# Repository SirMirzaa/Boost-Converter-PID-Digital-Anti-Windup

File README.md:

# Boost Converter dengan Kontrol PID Digital + Anti-Windup
Teknologi Rekayasa Instrumentasi dan Kontrol, SV UGM.

Proyek ini punya dua tahap dengan spesifikasi berbeda:

1. **Simulasi (UTS): paket PBL-B dari dosen**, 24 V → 48 V. Sudah selesai di Simulink (`simulink/`).
2. **Hardware (UAS): reverse engineering modul MT3608**, 12 V → 24 V. Board dibuat dengan MOSFET dan gate driver diskret, dikendalikan RP2040 dengan PID digital + anti-windup. Telemetri dikirim ke board IoT (ESP32-C3) lewat UART.

## Spesifikasi hardware (reverse MT3608)

| Parameter | Nilai |
|---|---|
| Vin | 12 V (adaptor 12 V 2 A) |
| Vout (Vref) | 24 V (bisa diatur, maks 28 V) |
| fsw | 300 kHz |
| Induktor | 22 µH, CD54 (dicopot dari modul MT3608) |
| Beban | 220 Ω dan 110 Ω (2 × 220 Ω paralel) |
| Iout nominal | ±0,22 A (110 Ω) |
| Gangguan | 220 Ω → 110 Ω |
| Ripple Vout | ≤ 0,48 Vpp (2 %) |

Arus dibatasi induktor CD54 (arus saturasi sekitar 1–1,5 A). Converter bekerja di batas CCM/DCM, sama seperti MT3608 di beban ringan.

## Spesifikasi simulasi (PBL-B, sudah selesai)

| Parameter | Nilai |
|---|---|
| Vin | 24 V (uji 20 / 24 / 28 V) |
| Vref | 48 V |
| fsw | 20 kHz |
| Beban | 32 Ω nominal, uji 16–64 Ω |
| Ripple Vout | ≤ 0,96 Vpp |
| Gangguan | 32 Ω → 16 Ω pada t = 0,05 s |

## Progres

- [x] Perhitungan dan model Simulink PBL-B (open-loop, closed-loop)
- [x] Tuning PID, 8 kombinasi gain (`simulink/tuning_pid.m`)
- [x] Skrip uji skenario (`simulink/uji_skenario.m`)
- [x] Revisi skematik KiCad ke spek MT3608 (ERC bersih)
- [x] Footprint CD54 + model 3D
- [ ] Simulink untuk spek hardware (12 V → 24 V, 300 kHz, 22 µH)
- [ ] Verifikasi Proteus (gate driver)
- [ ] Layout dan routing PCB, cetak PCB
- [ ] Firmware RP2040 (PWM 300 kHz, PID, telemetri UART)
- [ ] Uji hardware dan perbandingan dengan modul MT3608 asli

## Struktur repo

```
docs/        rencana kerja, perhitungan, laporan, gambar
simulink/    model .slx + skrip .m (PBL-B)
hardware/    kicad/ (skematik, PCB, footprint, model 3D), proteus/, BOM.csv
firmware/    kode RP2040 (PID digital + anti-windup, telemetri ke ESP32-C3)
data/        hasil pengukuran / log telemetri (.csv)
```

Rencana kerja: [docs/PLANNING.md](docs/PLANNING.md) · Daftar komponen: [hardware/BOM.csv](hardware/BOM.csv) · Panduan Simulink: [docs/SIMULINK_GUIDE.md](docs/SIMULINK_GUIDE.md)

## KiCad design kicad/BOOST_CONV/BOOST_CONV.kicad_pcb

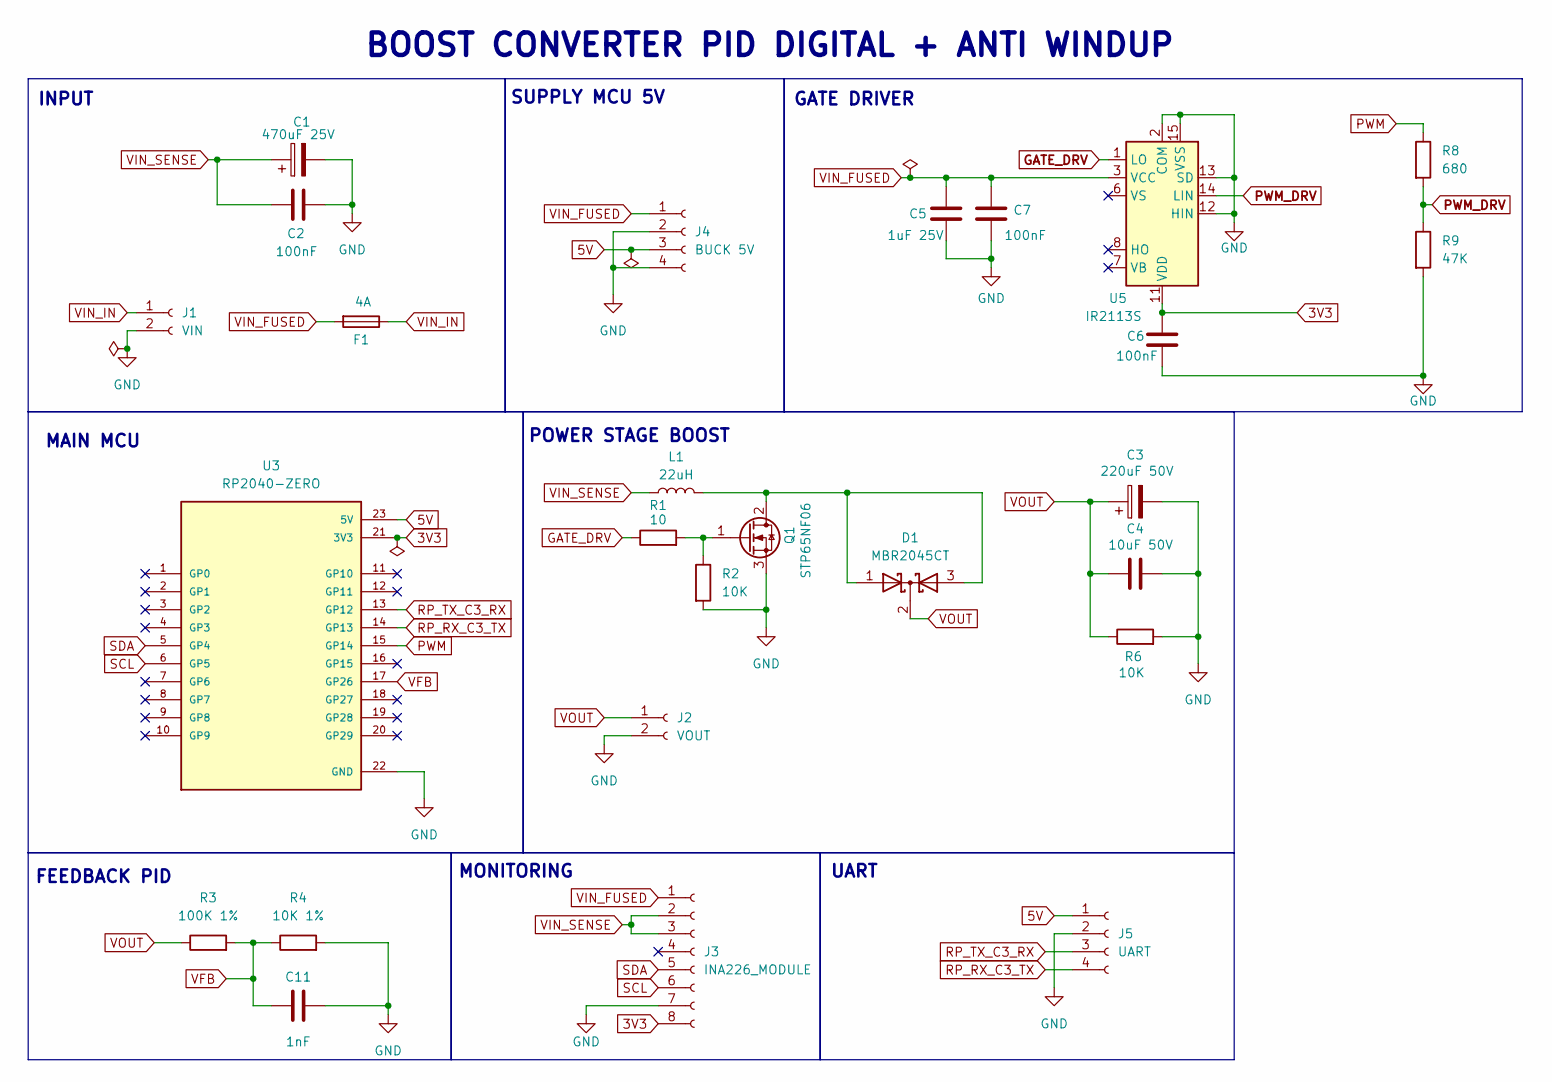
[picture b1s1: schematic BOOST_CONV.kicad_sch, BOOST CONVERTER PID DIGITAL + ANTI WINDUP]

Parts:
C1: 470uF 25V; CP_Radial_D10.0mm_P5.00mm
C2, C6, C7: 100nF; C_1206_3216Metric
C3: 220uF 50V; CP_Radial_D12.5mm_P5.00mm
C4: 10uF 50V; C_1206_3216Metric
C5: 1uF 25V; C_1206_3216Metric
C11: 1nF; C_1206_3216Metric
D1: MBR2045CT; TO-220-3_Vertical
F1: 4A; Fuseholder_Cylinder-5x20mm_Bulgin_FX0457_Horizontal_Closed
J1: VIN; TerminalBlock_Phoenix_MKDS-1,5-2_1x02_P5.00mm_Horizontal
J2: VOUT; TerminalBlock_Phoenix_MKDS-1,5-2_1x02_P5.00mm_Horizontal
J3: INA226_MODULE; PinSocket_1x08_P2.54mm_Vertical
J4: BUCK 5V; Mini560
J5: UART; JST_XH_B4B-XH-A_1x04_P2.50mm_Vertical
L1: 22uH; L_Sumida_CD54_5.8x5.2mm
Q1: STP65NF06; TO-220-3_Vertical
R1: 10; R_1206_3216Metric
R2, R6: 10K; R_0805_2012Metric
R3: 100K 1%; R_0805_2012Metric
R4: 10K 1%; R_0805_2012Metric
R8: 680; R_0805_2012Metric
R9: 47K; R_0805_2012Metric
U3: RP2040-ZERO; MODULE_RP2040-ZERO; PARTREV NA
U5: IR2113S; SOIC-16W_7.5x10.3mm_P1.27mm

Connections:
3V3: C6.1, J3.8, U3.21 (3V3), U5.11 (VDD)
5V: J4.3, J5.1, U3.23 (5V)
GATE_DRV: R1.1, U5.1 (LO)
GND: C1.2, C2.1, C3.2, C4.2, C5.2, C6.2, C7.2, C11.2, J1.2, J2.2, J3.7, J4.2, J4.4, J5.2, Q1.3 (S), R2.2, R4.2, R6.2, R9.2, U3.22 (GND), U5.2 (COM), U5.12 (HIN), U5.13 (SD), U5.15 (VSS)
unnamed: D1.1 (A), D1.3 (A), L1.2, Q1.2 (D)
unnamed: Q1.1 (G), R1.2, R2.1
PWM: R8.1, U3.15 (GP14)
PWM_DRV: R8.2, R9.1, U5.14 (LIN)
RP_RX_C3_TX: J5.4, U3.14 (GP13)
RP_TX_C3_RX: J5.3, U3.13 (GP12)
SCL: J3.6, U3.6 (GP5)
SDA: J3.5, U3.5 (GP4)
VFB: C11.1, R3.2, R4.1, U3.17 (GP26)
VIN_FUSED: C5.1, C7.1, F1.2, J3.1, J4.1, U5.3 (VCC)
VIN_IN: F1.1, J1.1
VIN_SENSE: C1.1, C2.2, J3.2, J3.3, L1.1
VOUT: C3.1, C4.1, D1.2 (K), J2.1, R3.1, R6.1

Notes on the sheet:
SUPPLY MCU 5V
GATE DRIVER
MAIN MCU
BOOST CONVERTER PID DIGITAL + ANTI WINDUP
UART
FEEDBACK PID
INPUT
MONITORING
POWER STAGE BOOST

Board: 2 copper layers, 26 parts (0 on the bottom side), 17 nets, no tracks yet.

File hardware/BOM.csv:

Ref,Komponen,Nilai / Part,Footprint,Jumlah,Catatan
L1,Induktor daya,22 uH CD54 (dari modul MT3608),PBL_Boost:L_Sumida_CD54_5.8x5.2mm,1,Isat sekitar 1-1.5 A; batasi Iout +/-0.22 A
Q1,MOSFET N-channel,STP65NF06,TO-220-3_Vertical,1,60 V; tab = SW; isolasi bila satu heatsink dengan D1
D1,Dioda Schottky ganda,MBR2045CT,TO-220-3_Vertical,1,Pin 1 & 3 ke SW; pin 2 (tab) ke VOUT
U5,Gate driver,IR2113S (pakai LO saja),SOIC-16W_7.5x10.3mm_P1.27mm,1,VDD 3V3; VCC Vin; HIN & SD ke GND
U3,Mikrokontroler,RP2040-Zero / RP2040 Super Mini,RP2040-ZERO:MODULE_RP2040-ZERO,1,GP14 PWM; GP26 VFB; GP4/5 I2C; GP12/13 UART
J4,Buck 5 V,Mini560 5V,MINI560:Mini560,1,Input dari VIN_FUSED; suplai RP2040 + ESP32-C3
J3,Sensor arus & tegangan input,Modul INA226 (shunt R100 bawaan),PinSocket_1x08_P2.54mm_Vertical,1,Arus input lewat modul; batas baca +/-0.82 A
C1,Elco input,470 uF 25 V (Sanyo 8x12 mm),CP_Radial_D8.0mm_P3.50mm,1,Di sisi VIN_SENSE dekat L1
C2,Keramik input,100 nF,C_1206_3216Metric,1,
C3,Elco output,220 uF 50 V low-ESR,CP_Radial_D10.0mm_P5.00mm,1,Belum dibeli; ukur sebelum cetak PCB
C4,Keramik output,10 uF 50 V,C_1206_3216Metric,1,Tambah 1 lagi paralel bila ada
R6,Resistor bleeder output,10 kOhm,R_Axial_DIN0414,1,
C5,Decoupling VCC driver,1 uF 25 V,C_1206_3216Metric,1,Dekat pin VCC U5
C7,Decoupling VCC driver,100 nF,C_1206_3216Metric,1,Dekat pin VCC U5
C6,Decoupling VDD driver,100 nF,C_1206_3216Metric,1,Dekat pin VDD U5
R1,Resistor gate,10 Ohm,R_1206_3216Metric,1,4.7-10 Ohm
R2,Resistor gate-source,10 kOhm,R_0805_2012Metric,1,Menjaga MOSFET mati saat boot
R8,Resistor seri PWM,680 Ohm,R_0805_2012Metric,1,
R9,Pull-down PWM_DRV,47 kOhm,R_0805_2012Metric,1,
R3,Pembagi feedback atas,100 kOhm 1%,R_0805_2012Metric,1,24 V -> 2.18 V
R4,Pembagi feedback bawah,10 kOhm 1%,R_0805_2012Metric,1,
C11,Filter feedback,1 nF,C_1206_3216Metric,1,Dekat GP26
F1,Fuse,4 A kaca 5x20 mm (2 A disarankan) + holder,Fuseholder 5x20 (cocokkan dengan holder),1,
J1,Konektor input,KF301-2P,TerminalBlock_Phoenix_MKDS-1.5-2_1x02_P5.00mm_Horizontal,1,
J2,Konektor output,KF301-2P,TerminalBlock_Phoenix_MKDS-1.5-2_1x02_P5.00mm_Horizontal,1,
J5,Konektor UART ke ESP32-C3,JST-XH 4P / pin header 1x4,JST_XH_B4B-XH-A_1x04_P2.50mm_Vertical,1,5V; GND; TX; RX
HS,Heatsink,TO-220 + mika + ring isolator,,1 set,
Load,Beban uji,2x resistor kapur 220 Ohm 10 W,,2,220 Ohm atau 110 Ohm (paralel)
PSU,Sumber,Adaptor 12 V 2 A regulated,,1,Jangan sampai turun di bawah +/-10.5 V (batas IR2113)
